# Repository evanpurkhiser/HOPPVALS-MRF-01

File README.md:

<p align="center">
  <picture>
    <source media="(prefers-color-scheme: dark)" srcset="docs/images/carriage-hero-dark.png">
    
  </picture>
</p>

# HOPPVALS-MRF-01

**IKEA HOPPVALS Motorized Retrofit, version 01** (short: **HV-MRF-01**).

An open hardware + firmware project
that motorizes an [IKEA HOPPVALS][hoppvals] cellular (honeycomb) blind
and exposes it to your smart home as a standard **Zigbee 3.0 Window Covering** —
so any compliant hub (Home Assistant / ZHA, Zigbee2MQTT, deCONZ, SmartThings)
can drive it with no custom converters.

Two synchronized DC gearmotors wind the blind's lift cords onto grooved drums to
raise and lower the shade.
A custom ESP32-C6 controller board fits inside the head rail
and runs the firmware in this repo.

> Status: work in progress —
> hardware and firmware are still under active development.

## Repository layout

| Path           | Contents                                                       |
| -------------- | -------------------------------------------------------------- |
| `firmware/`    | ESP32-C6 firmware (ESP-IDF, C++) — the Zigbee controller       |
| `electronics/` | KiCad schematic + PCB for the controller board                 |
| `mechanical/`  | Fusion 360 designs for the motor/drum/carriage assembly        |
| `docs/`        | Design write-ups, datasheets, schematic/PCB exports            |
| `tools/`       | Python scripts for bench diagnostics and motion tuning         |

## Documentation

- [`docs/DESIGN.md`](docs/DESIGN.md) — system design: mechanics, motion control,
  Zigbee behavior, and the reasoning behind it.

## Building Firmware

The firmware uses ESP-IDF for the `esp32c6` target.
The repo keeps the ESP-IDF checkout and tools local to the project:

- `.esp-idf/` — ESP-IDF checkout
- `.idf_tools/` — ESP-IDF toolchains and Python environment

Bootstrap the local toolchain once:

```sh
make -C firmware bootstrap
```

Build the firmware:

```sh
make -C firmware build
```

Other useful firmware targets:

```sh
make -C firmware flash PORT=/dev/ttyACM0
make -C firmware monitor PORT=/dev/ttyACM0
make -C firmware ota IP=<device-ip>
```

Run `make -C firmware help` for the full target list.

[hoppvals]: https://www.ikea.com/us/en/p/hoppvals-cellular-blind-white-70431402/

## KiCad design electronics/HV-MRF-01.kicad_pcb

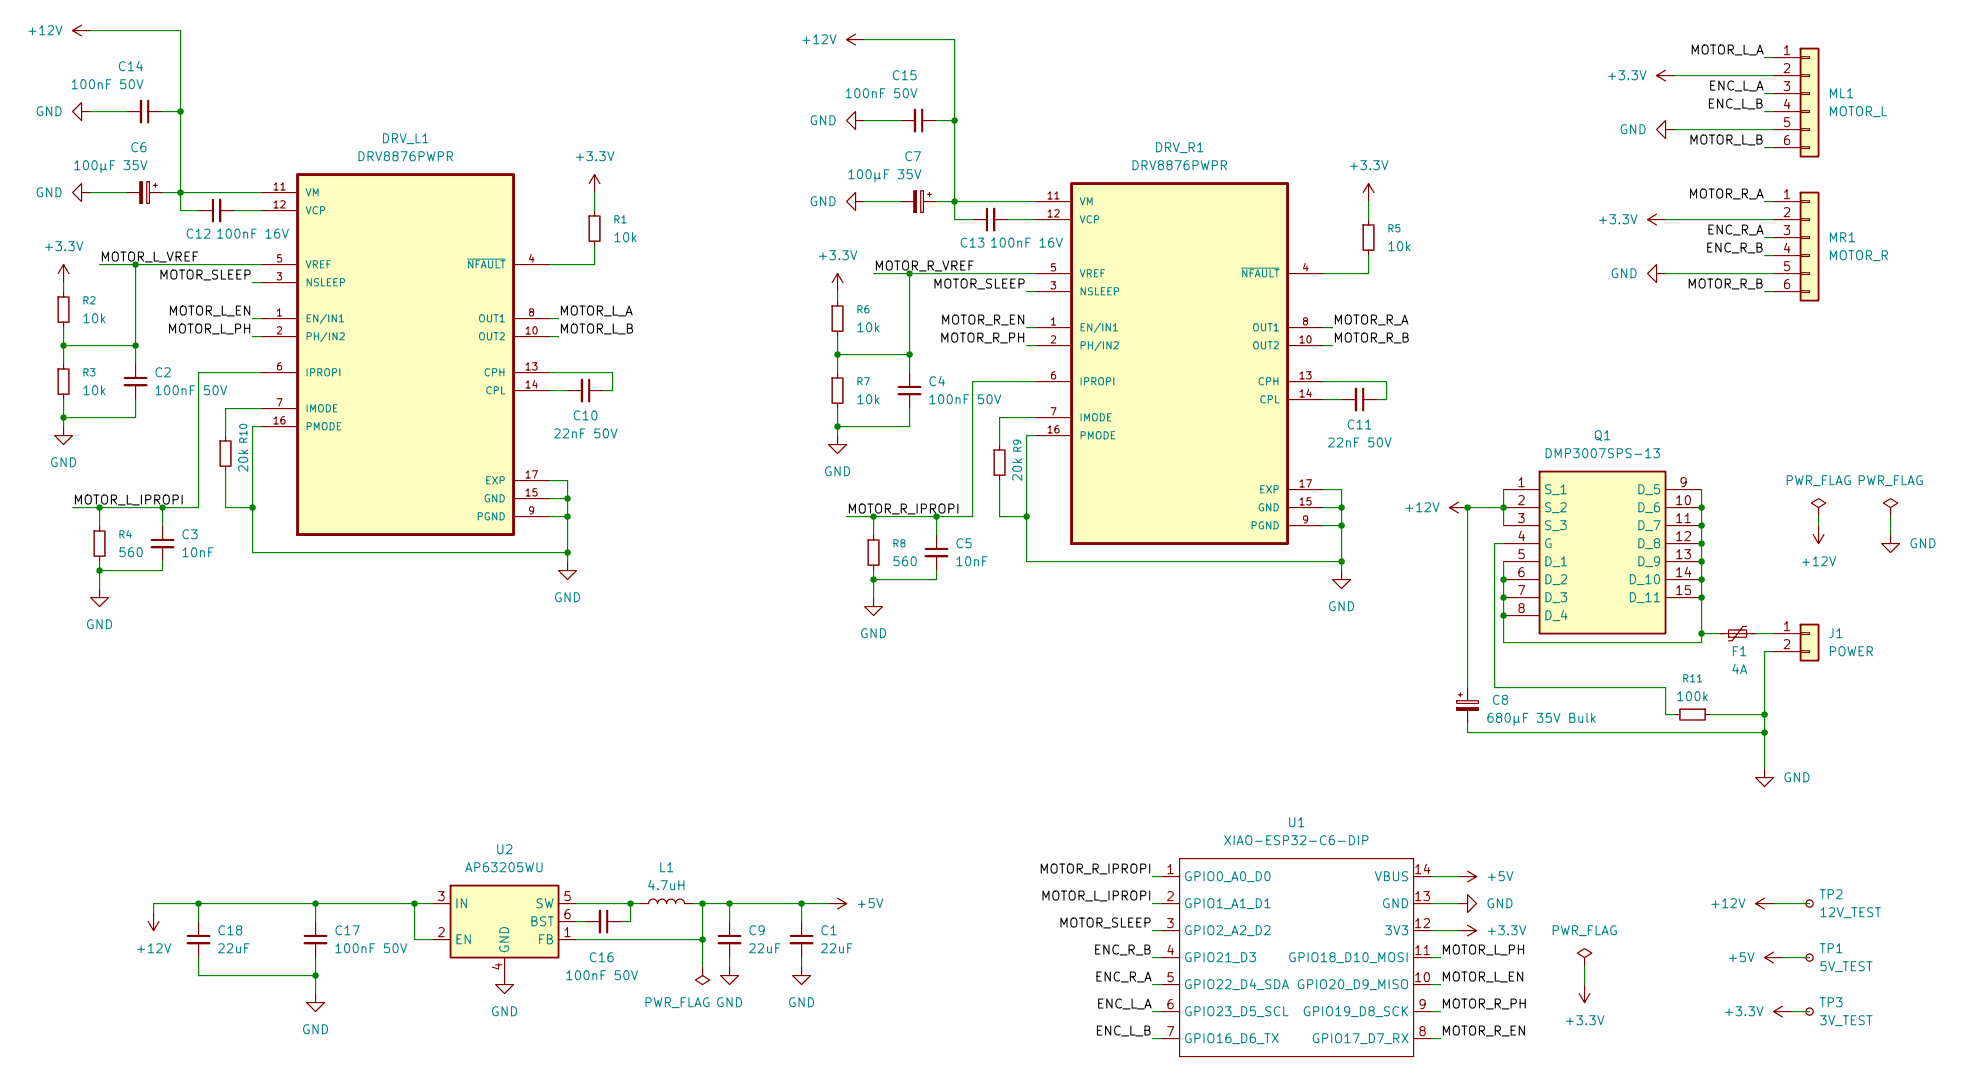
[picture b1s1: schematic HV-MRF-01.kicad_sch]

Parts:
C1, C9, C18: 22uF; C_1210_3225Metric; LCSC C12891
C2, C4, C14, C15, C16, C17: 100nF 50V; C_0603_1608Metric; LCSC C14663
C3, C5: 10nF; C_0603_1608Metric; LCSC C57112
C6, C7: 100µF 35V; CP_Elec_6.3x7.7; LCSC C2983322
C8: 680µF 35V Bulk; CP_Elec_10x10.5; LCSC C7461236
C10, C11: 22nF 50V; C_0603_1608Metric; LCSC C21122
C12, C13: 100nF 16V; C_0402_1005Metric; LCSC C1525
DRV_L1: DRV8876PWPR; PARTREV E; LCSC C575551
DRV_R1: DRV8876PWPR; PARTREV E; LCSC C575551
F1: 4A; Fuse_2920_7451Metric; LCSC C20539726
J1: POWER; TerminalBlock_CUI_TB007-508-02_1x02_P5.08mm_Horizontal
L1: 4.7uH; L_Changjiang_FNR4012S; LCSC C167781
ML1: MOTOR_L; JST_PH_B6B-PH-K_1x06_P2.00mm_Vertical
MR1: MOTOR_R; JST_PH_B6B-PH-K_1x06_P2.00mm_Vertical
Q1: DMP3007SPS-13; Mouser Part Number 621-DMP3007SPS-13
R1, R2, R3, R5, R6, R7: 10k; R_0603_1608Metric; LCSC C25804
R4, R8: 560; R_0603_1608Metric; LCSC C23204
R9, R10: 20k; R_0603_1608Metric; LCSC C4184
R11: 100k; R_0603_1608Metric; LCSC C25803
TP1: 5V_TEST; TestPoint_Pad_1.5x1.5mm
TP2: 12V_TEST; TestPoint_Pad_1.5x1.5mm
TP3: 3V_TEST; TestPoint_Pad_1.5x1.5mm
U1: XIAO-ESP32-C6-DIP
U2: AP63205WU; TSOT-23-6; LCSC C2071056

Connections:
+3.3V: ML1.2, MR1.2, R1.1, R2.1, R5.1, R6.1, TP3.1 (1_1), U1.12 (3V3)
+5V: C1.1, C9.1, L1.2, TP1.1 (1_1), U1.14 (VBUS), U2.1 (FB)
+12V: C6.1, C7.1, C8.1, C12.1, C13.1, C14.1, C15.1, C17.1, C18.1, DRV_L1.11 (VM), DRV_R1.11 (VM), Q1.1 (S_1), Q1.2 (S_2), Q1.3 (S_3), TP2.1 (1_1), U2.2 (EN), U2.3 (IN)
/ENC_L_A: ML1.3, U1.6 (GPIO23_D5_SCL)
/ENC_L_B: ML1.4, U1.7 (GPIO16_D6_TX)
/ENC_R_A: MR1.3, U1.5 (GPIO22_D4_SDA)
/ENC_R_B: MR1.4, U1.4 (GPIO21_D3)
/MOTOR_L_A: DRV_L1.8 (OUT1), ML1.1
/MOTOR_L_B: DRV_L1.10 (OUT2), ML1.6
/MOTOR_L_EN: DRV_L1.1 (EN/IN1), U1.10 (GPIO20_D9_MISO)
/MOTOR_L_IPROPI: C3.1, DRV_L1.6 (IPROPI), R4.1, U1.2 (GPIO1_A1_D1)
/MOTOR_L_PH: DRV_L1.2 (PH/IN2), U1.11 (GPIO18_D10_MOSI)
/MOTOR_L_VREF: C2.1, DRV_L1.5 (VREF), R2.2, R3.1
/MOTOR_R_A: DRV_R1.8 (OUT1), MR1.1
/MOTOR_R_B: DRV_R1.10 (OUT2), MR1.6
/MOTOR_R_EN: DRV_R1.1 (EN/IN1), U1.8 (GPIO17_D7_RX)
/MOTOR_R_IPROPI: C5.1, DRV_R1.6 (IPROPI), R8.1, U1.1 (GPIO0_A0_D0)
/MOTOR_R_PH: DRV_R1.2 (PH/IN2), U1.9 (GPIO19_D8_SCK)
/MOTOR_R_VREF: C4.1, DRV_R1.5 (VREF), R6.2, R7.1
/MOTOR_SLEEP: DRV_L1.3 (NSLEEP), DRV_R1.3 (NSLEEP), U1.3 (GPIO2_A2_D2)
GND: C1.2, C2.2, C3.2, C4.2, C5.2, C6.2, C7.2, C8.2, C9.2, C14.2, C15.2, C17.2, C18.2, DRV_L1.9 (PGND), DRV_L1.15 (GND), DRV_L1.16 (PMODE), DRV_L1.17 (EXP), DRV_R1.9 (PGND), DRV_R1.15 (GND), DRV_R1.16 (PMODE), DRV_R1.17 (EXP), J1.2, ML1.5, MR1.5, R3.2, R4.2, R7.2, R8.2, R9.2, R10.2, R11.1, U1.13 (GND), U2.4 (GND)
unnamed: C10.1, DRV_L1.13 (CPH)
unnamed: C10.2, DRV_L1.14 (CPL)
unnamed: DRV_L1.7 (IMODE), R10.1
unnamed: C12.2, DRV_L1.12 (VCP)
unnamed: DRV_L1.4 (~NFAULT), R1.2
unnamed: C11.1, DRV_R1.13 (CPH)
unnamed: C11.2, DRV_R1.14 (CPL)
unnamed: DRV_R1.7 (IMODE), R9.1
unnamed: C13.2, DRV_R1.12 (VCP)
unnamed: DRV_R1.4 (~NFAULT), R5.2
unnamed: F1.2, J1.1
unnamed: F1.1, Q1.5 (D_1), Q1.6 (D_2), Q1.7 (D_3), Q1.8 (D_4), Q1.9 (D_5), Q1.10 (D_6), Q1.11 (D_7), Q1.12 (D_8), Q1.13 (D_9), Q1.14 (D_10), Q1.15 (D_11)
unnamed: Q1.4 (G), R11.2
unnamed: C16.2, U2.6 (BST)
unnamed: C16.1, L1.1, U2.5 (SW)

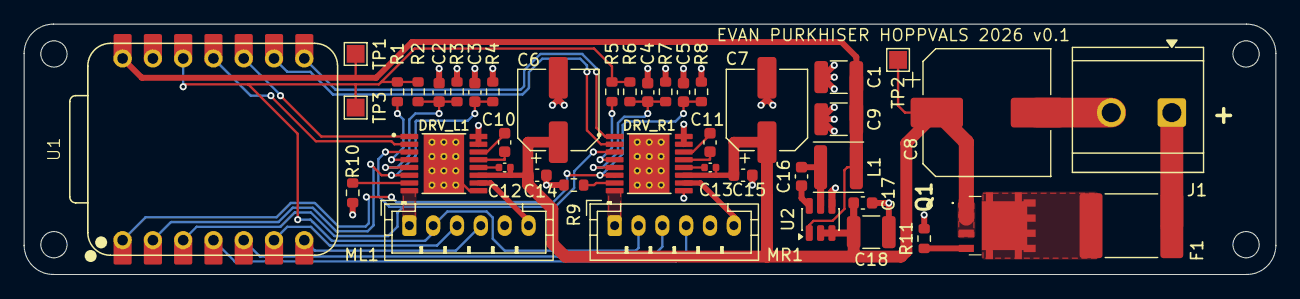
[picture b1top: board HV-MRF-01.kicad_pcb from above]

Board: 2 copper layers, 105.0 x 21.0 mm, 46 parts (0 on the bottom side), 36 nets.

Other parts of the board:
H1, H2, H3, H4: MountingHole_2.2mm_M2

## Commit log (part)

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2026-05-24 Initial project scaffold for Zigbee-controlled IKEA HOPPVALS blinds
    ESP-IDF v5.3 project targeting XIAO ESP32-C6, using the esp-zigbee-lib
    managed component. Includes a stub Zigbee Router skeleton that builds
    end-to-end but does not yet register the Window Covering endpoint.
    DESIGN.md captures the full plan: mechanical layout (two-motor cord
    drive on a level-wind lead screw), pin allocation, motion control
    strategy (trapezoidal velocity profile with closed-loop PID per motor,
2026-06-15 Reorganize into top-level firmware/electronics/mechanical/docs/tools layout
    The project is growing beyond firmware: it will also house the mechanical
    design (Fusion 360) and electronics (KiCad schematic + PCB), plus a set of
    diagnostic/benchmark tools. Give each its own top-level home and move the
    existing ESP-IDF project under firmware/ and the design docs under docs/ so
    there is room to bring the other components in.
    Pure relocation only; firmware internals and the in-progress refactor are
2026-06-15 Restructure firmware into ESP-IDF components with motion control
    Replace the single-file blinds.c/.h Zigbee skeleton with a component-based
    C++23 architecture. The old code only logged commissioning lifecycle events
    and registered an empty endpoint; this builds out the full device.
    The zigbee component now owns the stack and presents a real Window Covering
    endpoint, dispatching cover commands synchronously to registered handlers and
    publishing notifications over an esp_event bus. Cover commands route through
2026-06-15 Fix IKEA HOPPVALS product link in README
2026-06-15 Add styled carriage line-render as README hero
    Render the drive-carriage model as a hidden-line technical illustration in
    Blender (Freestyle): blueprint-blue for light mode, amber for dark, with a
    floor grid and HV-MRF-01 title block. A <picture> element in the README swaps
    them via prefers-color-scheme. Blender source kept in assets/.
2026-06-15 Enlarge README hero title block text
2026-06-15 Add electronics build badge to README
2026-06-15 Register KiCad stock libraries in electronics CI
    Copy KiCad's bundled global sym/fp library tables into the container's
    config before running ERC/DRC so stock symbols (power, Device, Resistor_SMD,
    ...) stop reporting as 'not in the current configuration'. Cosmetic only —
    the symbols are cached in the design files, so checks already evaluated
    correctly; this just removes the warning noise from CI logs.
2026-06-15 Add firmware build CI and badge
    Build the ESP-IDF firmware (esp32c6, IDF v5.3.2) via the official
    espressif/esp-idf-ci-action on changes under firmware/, and upload the
    flashable binary set (app, bootloader, partition table) plus the elf as an
    artifact. Add a matching firmware badge to the README.
2026-06-15 Report firmware git SHA via Zigbee SWBuildID
    ESP-IDF bakes the `git describe` output (short commit SHA, with a
    -dirty suffix for uncommitted builds) into the app descriptor at build
    time. Expose it through the Basic cluster's SWBuildID attribute so
    ZHA/Z2M report which firmware revision a flashed device is running in
    Home Assistant.
2026-06-15 Rename Firwmare workflow -> ERC
2026-06-15 Fix raise direction and encoder sign for as-built PCB
    Two conventions carried over from the breadboard prototype were wrong for
    the as-built PCB and caused `raise` to physically lower while tripping the
    motion sync watchdog:
    - encoder: dropped the Right-only count negation. On the PCB both encoders
    count the same hardware direction, so negating R split L/R apart and
    pushed |L - R| past the sync-fault limit within ~90 ms.
2026-06-16 Add config editing and remote console dispatch to CLI
    Route command output through emit() instead of printf so it can be captured.
    emit() writes to a thread_local string buffer during remote dispatch (so a
    command on one task can't redirect another task's output) and to stdout
    otherwise. run_line() runs a single command line and returns its captured
    output, serialized by a mutex since esp_console_run() isn't re-entrant;
    init_for_remote() registers the command set without the USB REPL.
2026-06-16 Add WiFi debug mode with websocket console
    When the one-shot debug flag is set (via the `debug` CLI command, later over
    Zigbee), boot brings up WiFi as a station instead of starting Zigbee and
    serves the command console over a websocket at /ws — so the full CLI and
    benchmarks are reachable without a USB cable. The 2.4 GHz radio is shared
    with Zigbee, so the two never run in the same boot.
    The flag is cleared on read, so any crash or power-cycle returns to normal
2026-06-16 Add HTTP firmware push (OTA) in WiFi debug mode
    Split the single factory app partition into ota_0/ota_1 so a new image can be
    written to the inactive slot, and enable bootloader rollback so an image that
    can't boot or get on WiFi self-heals to the previous slot instead of bricking
    a mounted, USB-less device. Applying this layout needs one last USB flash;
    after that, updates go over WiFi.
    http_debug serves POST /ota: stream the body through the standard esp_ota_ops
2026-06-16 De-energize motors during OTA write
    Pull nSLEEP low (via the new motor::disable) at the start of the /ota handler,
    after stopping the motion controller so its loop can't re-wake the drivers.
    The motors are then guaranteed off and unable to run for the duration of the
    flash write and the reboot, regardless of what the incoming image does on boot.
2026-06-21 Fix one motor driving itself on boot
    configure_gpio() woke the drivers (nSLEEP high) before configure_ledc() drove
    the EN pins to 0 — and EN isn't in configure_gpio's pin mask, so it floated.
    A floating-high EN with the driver awake and PH=0 drives that motor full-tilt
    in one direction until LEDC clamps EN low, which is why a motor would run on
    boot. Keep the drivers asleep through pin setup and only wake them into brake
    (nSLEEP high + EN=0) after configure_ledc() has forced EN low.
2026-06-21 Stop and sleep motors before rebooting
    The debug-switch, recovery-timeout, and `debug`-command reboot paths now halt
    the control loop and pull nSLEEP low before esp_restart(), matching what the
    OTA path already does, so the motors are never mid-drive across a reset.
2026-06-21 Add WiFi debug-console web control app
    A Vite + React + TS single-page app (tools/control) that talks to the device's
    debug-mode websocket: connection bar, a config form built from the live
    `config` dump (editable motion.* fields, read-only net.*), hold-to-move motion
    control (↑/W raise, ↓/S lower, release stops) with a repeat guard and
    multi-path stop-safety, a Home button (long-timeout `home`), and a timestamped
    console with a raw-command box. Plain http dev server so ws:// isn't blocked.
2026-06-21 Show descriptions under each config field
    Add a one-line explanation to every config field and render it under the
    label (grid layout: label + description stacked, input on the right). Also
    adds the three homing fields (home_duty/settle/timeout) that were missing
    from the form.
2026-06-22 Add open-loop characterization sweep harness
    Host tooling (tools/characterization) that drives the `profile` command over
    the debug websocket across a duty sweep — for each duty: home, profile down,
    profile up, home — saving per-run CSVs (position, current, derived velocity and
    acceleration per motor) and generating per-run and summary graphs (steady RPM
    vs duty, current vs duty). sweep.py is pure stdlib so the physical run can't
    fail on a missing package; plot.py uses numpy/matplotlib.
2026-06-22 Add feedforward, go-to-%, and travel-limit controls to web app
    Config form gains the feedforward offset, mm/rev, and hard/soft stop fields
    (with descriptions), and the motion panel gets a "Go to %" input + button that
    sends gotopct with a long timeout (the move blocks on the device).
2026-06-22 Default mm_per_rev from drum geometry
    The grooved level-wound drum is 22 mm effective diameter and turns 1:1 with
    the output shaft, so mm/rev = pi x 22 ~= 69.1 (cord runs direct to the bottom
    rail). Same drum on every unit, so bake it as the default instead of leaving
    go-to uncalibrated (0). Refine per-device only if a build differs.
2026-06-22 Make go-to non-blocking and its approach configurable
    Stop wasn't interrupting a go-to from the UI: the blocking gotopct/goto handler
    monopolized the single websocket connection for the whole move, so `motion
    stop` couldn't be read until the move finished. Switch the console (and the
    app, via it) to the non-blocking begin_go_to_* — the move runs in the control
    task and the handler returns immediately, so stop is processed promptly and
    cancels it. (Matches the cover model anyway; the blocking go_to_* remain as API.)
2026-06-22 Web app: grouped config, go-to speed, and FF trim fields
    Restructure the config form into titled sections/subsections (Travel & Limits,
    WiFi, and a grouped Motion Tuning), each with a short blurb. The Go-to-%
    control now sends the RPM from the Motion panel, and the Feedforward group
    gains the per-motor ff_trim_l/ff_trim_r fields.
2026-06-22 Add trim auto-tuner and document the sync/wobble investigation
    tune_trim.py runs a closed-loop secant search on ff_trim_r to zero the steady
    L-R offset between the two motors (per-device; run once per unit).
    MOTOR_SYNC_INVESTIGATION.md records the whole thread: the ~5% open-loop motor
    mismatch and the feedforward-trim fix, and the separate once-per-revolution
    speed wobble that we traced — by ruling out trim, sync, and PI gains — to a
    mechanical, shaft-angle-locked cause on the left spool. Includes the
2026-06-23 Decouple motor, motion, and sensor components
    A design-review pass over the component graph turned up a dependency
    cycle and a couple of fake dependencies. Clean them up so every edge
    points downward and each shared type lives with the code that owns it:
    - Move the ZCL cover command handlers (open/close/stop/go-to) out of
    the motor driver and into motion, which already owns motor state.
    motor no longer depends on zigbee/config/motion, breaking the
2026-06-23 Report blind position over the console
    Give the web UI a way to track where the blind is. Add an emit_position()
    helper that prints a canonical, machine-parseable line:
    pos L=<mm> R=<mm> moving=<0|1> valid=<0|1>
    emitted by the `pos` command and appended to the `motion stop` reply, so the
    UI always learns the final position when a move ends. valid=0 flags a missing
    reference (not homed / mm_per_rev unset), so the mm figures are meaningless.
2026-06-23 Clean up code comments: drop dividers and fix stale docs
    A comment audit after the motor/motion decoupling turned up drift and
    some inconsistent style. This is a comments-only pass, no behavior change.
    - Strip flag-style section dividers (// ── Title ──, // ----) down to
    plain // Title, and separate each section header from its code with a
    blank line.
    - Fix descriptions left stale by the decouple refactor: main.cpp's
